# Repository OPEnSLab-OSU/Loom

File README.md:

<b>THIS VERSION OF LOOM HAS BEEN DEPRECATED AND IS NO LONGER BEING SUPPORTED, ANY BUGS YOU MAY ENCOUNTER WILL NOT BE FIXED PLEASE USE Loom 4</b>
https://github.com/OPEnSLab-OSU/Loom-V4

<p align="center">
    
  </a>
</p>

<h3 align="center">Loom</h3>
<p align="center">
  An Internet of Things Rapid Prototyping System for applications in environmental sensing
  <br>
  <a href="http://www.open-sensing.org/project-loom">Project Page</a>
  ·
  <a href="https://openslab-osu.github.io/Loom/html/index.html">Documentation</a>
  ·
  <a href="https://github.com/OPEnSLab-OSU/Loom/wiki">Lab Wiki</a>
  ·
  <a href=https://github.com/OPEnSLab-OSU/Loom/wiki/Quick-Start>Quick Start</a>
   ·
  <a href=https://github.com/OPEnSLab-OSU/Loom/wiki/Configuration>Configuration</a>
</p>

## Table of Contents

- [Table of Contents](#table-of-contents)
- [Introduction](#introduction)
- [Objectives](#objectives)
- [Key Features](#key-features)
- [Installing Arduino and Loom](#installing-arduino-and-loom)
- [Quick Start](#quick-start)
- [Common Pin Allocations](#common-pin-allocations)
- [Hardware Support](#hardware-support)
- [Documentation](#documentation)
- [Contributing](#contributing)
- [Versioning](#versioning)
- [Resources](#resources)
    - [Custom/Modified Libraries used by Loom](#custommodified-libraries-used-by-loom)
- [License](#license)

## Introduction

Loom is an ongoing multidisciplinary collaboration of the OPEnS Lab with a team of 20+ Computer Science and Electrical Engineering students to create a fully open source, modular, user friendly, sensor/actuator Arduino library and ecosystem. The project enables environmental research and conservation communities to overcome significant technical hurdles for creating new environmental, agricultural, and ecological instrumentation to measure, monitor, automate, and understand our world. 

## Objectives

- Design a "plug and play" sensor/actuator system
- Simple enough for K-12 students and non-technical users to use
- Extensible and programmable enough for engineers to customize
- Create a wide variety of applications by simply connecting modular components
- Make the system wireless, low-power, low latency
- Configure all sensors and actuators on a wireless network using an intuitive graphical user interface
- Interact with data and control signals on a network in realtime
- Make data transmitted from local and remote locations available instantly from anywhere around the world

## Key Features

- Quick to setup an entirely new project
- Code contained in an Arduino library
- System behavior defined with a configuration specification and minimal code
- Extensive customizability for complex applications
- Designed for extensibility
- Variety of sensors and actuators supported 
- Remote data logging to SD and internet in near real time

## Installing Arduino and Loom

[Installing Arduino and Loom Quick Setup](https://github.com/OPEnSLab-OSU/Loom/wiki/Arduino-and-Loom-Quick-Setup)

[Installing Arduino and Loom Manual Setup](https://github.com/OPEnSLab-OSU/Loom/wiki/Arduino-and-Loom-Manual-Setup)

## Quick Start

 [Quick Start Guide](https://github.com/OPEnSLab-OSU/Loom/wiki/Quick-Start)

## Common Pin Allocations

[Common Pin Allocations](https://github.com/OPEnSLab-OSU/Loom/wiki/Common-Pin-Allocations)

## Hardware Support

[Hardware Support](https://github.com/OPEnSLab-OSU/Loom/wiki/Hardware-Support)

## Documentation

[Wiki](https://wiki.open-sensing.org/doku.php?id=loom) for general documentation not on GitHub or in Doxygen document

[Doxygen generated documentation Version 1](https://openslab-osu.github.io/Loom/html/index.html) for more verbose documentation that is designed for developers

[Doxygen generated documentation Version 2](https://openslab-osu.github.io/Loom/index.html) for more user-friendly documenation that is designed for end-users

***Note***: The documentation does not currently update automatically, if would want to be sure you have the most up to date version of the documentation, you can run Doxygen to manually generate a local copy of the documentation. See the Doxygen website on how to [Install Doxygen](http://www.doxygen.nl/manual/install.html) and [Doxygen Usage](http://www.doxygen.nl/manual/doxygen_usage.html). 

Once installed, the run `doxygen Doxyfile` from the command line (from Loom directory) to generate the documentation. To view, open the `Loom/html/index.html` file in a browser.

## Contributing

Is there hardware support or other feature you would like to add to Loom? Follow our [Guide to contributing to Loom](https://github.com/OPEnSLab-OSU/Loom/wiki/Contributing-to-Loom)

## Versioning

Loom aims to follow [Semantic Versioning](https://semver.org) 

## Resources

- [Project Page](http://www.open-sensing.org/project-loom) for Loom on OPEnS lab website
- [GitHub Organization](https://github.com/OPEnSLab-OSU) for all OPEnS Lab projects
- [Loomify](https://github.com/OPEnSLab-OSU/Loomify) An npm package to drive the backend Loom Tag Format parsing and Loom Library github interactions.
- [Loom Configurator](https://github.com/OPEnSLab-OSU/Loom_Configurator) A WebApp designed for designing and exporting loom configurations
- [Loom-Network](https://github.com/OPEnSLab-OSU/Loom-Network) Arduino networking library designed for use with any wireless radio
- [Loom-Auxilliary](https://github.com/OPEnSLab-OSU/Loom_Auxiliary) General Loom and lab non-code files
- [Max-Loom2](https://github.com/OPEnSLab-OSU/Max-Loom2) MaxMSP interfaces for Loom interactivity

#### Custom/Modified Libraries used by Loom

- [OPEnS_RTC](https://github.com/OPEnSLab-OSU/OPEnS_RTC) A modified arduino library for with support for a variety of RTCs
- [SSLClient](https://github.com/OPEnSLab-OSU/SSLClient) Arduino library to add SSL functionality to any Client class 
- [EthernetLarge](https://github.com/OPEnSLab-OSU/EthernetLarge) Ethernet Library for Arduino, modified to support larger buffers for SSLClient

## License 

Loom is licensed under [GNU General Public License v3.0](https://github.com/OPEnSLab-OSU/Loom/blob/master/LICENSE)

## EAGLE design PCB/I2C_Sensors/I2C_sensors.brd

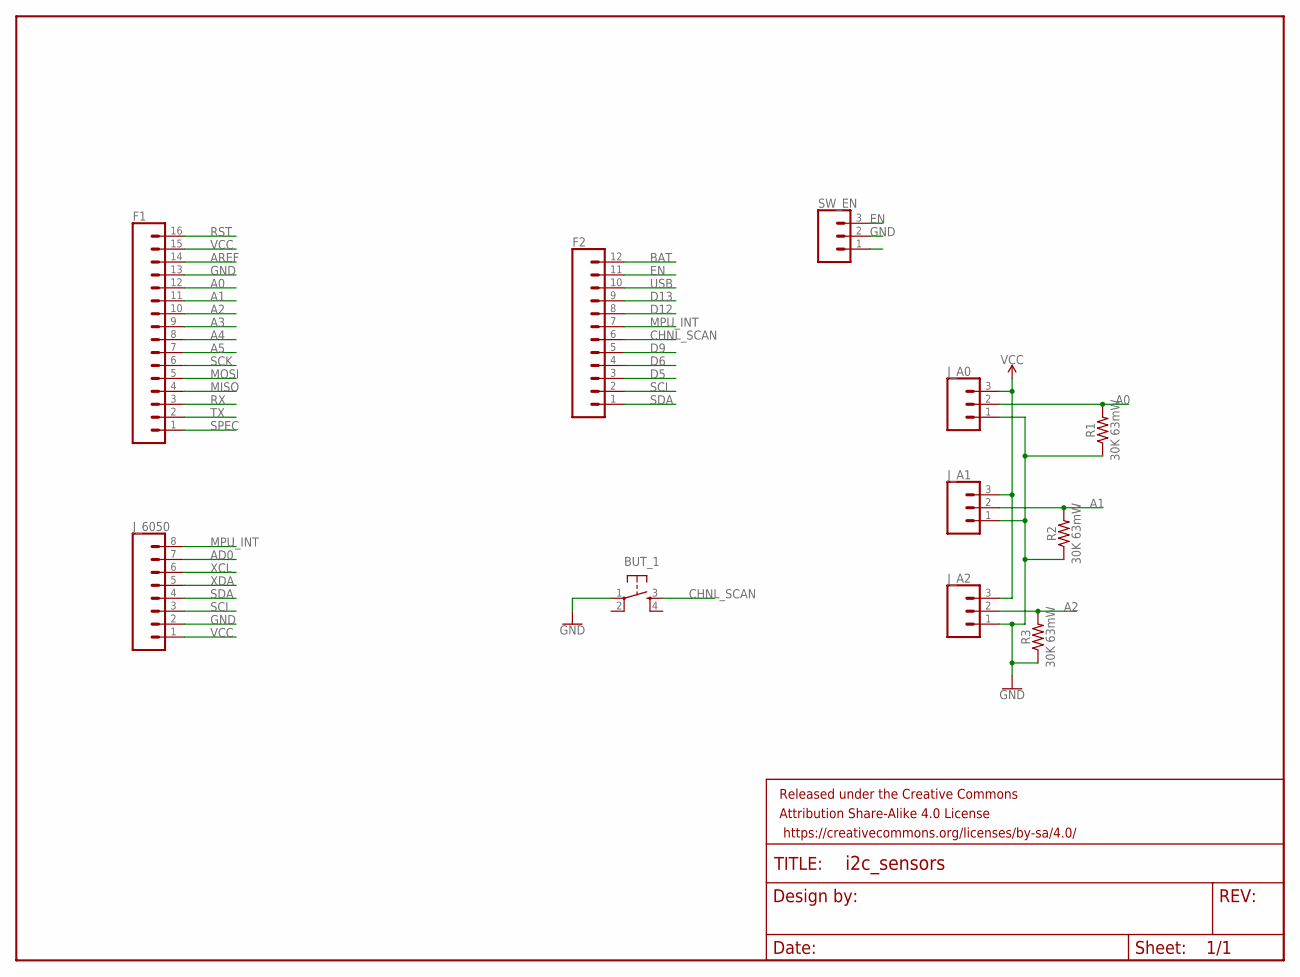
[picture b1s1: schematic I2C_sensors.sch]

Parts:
BUT_1: TAC_SWITCHPTH; TACTILE-PTH
F1: CONN_16; 1X16
F2: CONN_12; 1X12
FRAME1: FRAME-LETTER; CREATIVE_COMMONS
J_6050: CONN_08"; 1X08
J_A0, J_A1, J_A2: CONN_03JST-PTH-VERT; JST-3-PTH-VERT
R1, R2, R3: 30K 63mW; 0805
SW_EN: CONN_03; 1X03

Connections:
A0: F1.12, J_A0.2, R1.2
A1: F1.11, J_A1.2, R2.2
A2: F1.10, J_A2.2, R3.2
A3: F1.9
A4: F1.8
A5: F1.7
AD0: J_6050.7
AREF: F1.14
BAT: F2.12
CHNL_SCAN: BUT_1.3, F2.6
D5: F2.3
D6: F2.4
D9: F2.5
D12: F2.8
D13: F2.9
EN: F2.11, SW_EN.3
GND: BUT_1.1, F1.13, J_6050.2, J_A0.1, J_A1.1, J_A2.1, R1.1, R2.1, R3.1, SW_EN.2
MISO: F1.4
MOSI: F1.5
MPU_INT: F2.7, J_6050.8
RST: F1.16
RX: F1.3
SCI: F2.2, J_6050.3
SCK: F1.6
SDA: F2.1, J_6050.4
SPEC: F1.1
TX: F1.2
USB: F2.10
VCC: F1.15, J_6050.1, J_A0.3, J_A1.3, J_A2.3
XCL: J_6050.6
XDA: J_6050.5

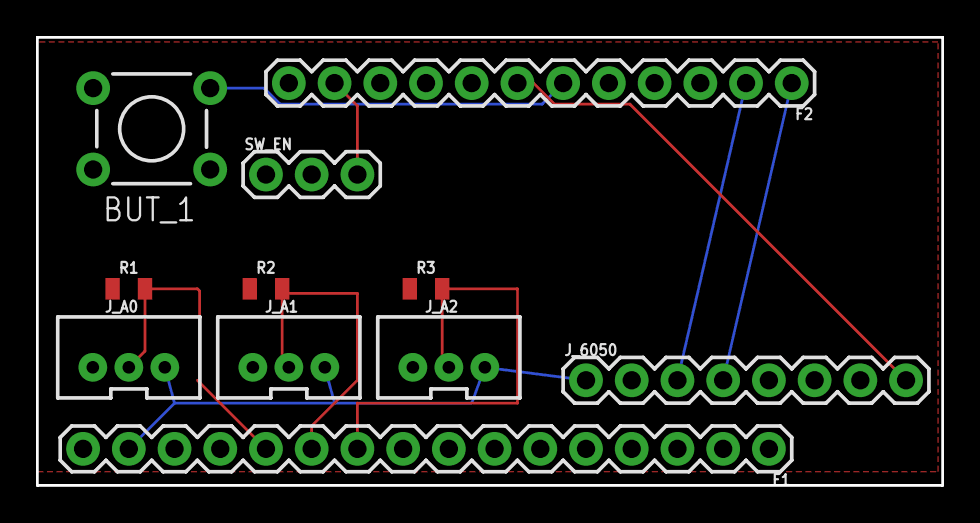
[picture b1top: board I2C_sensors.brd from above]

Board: 2 copper layers, 50.3 x 24.9 mm, 12 parts (0 on the bottom side), 10 nets.

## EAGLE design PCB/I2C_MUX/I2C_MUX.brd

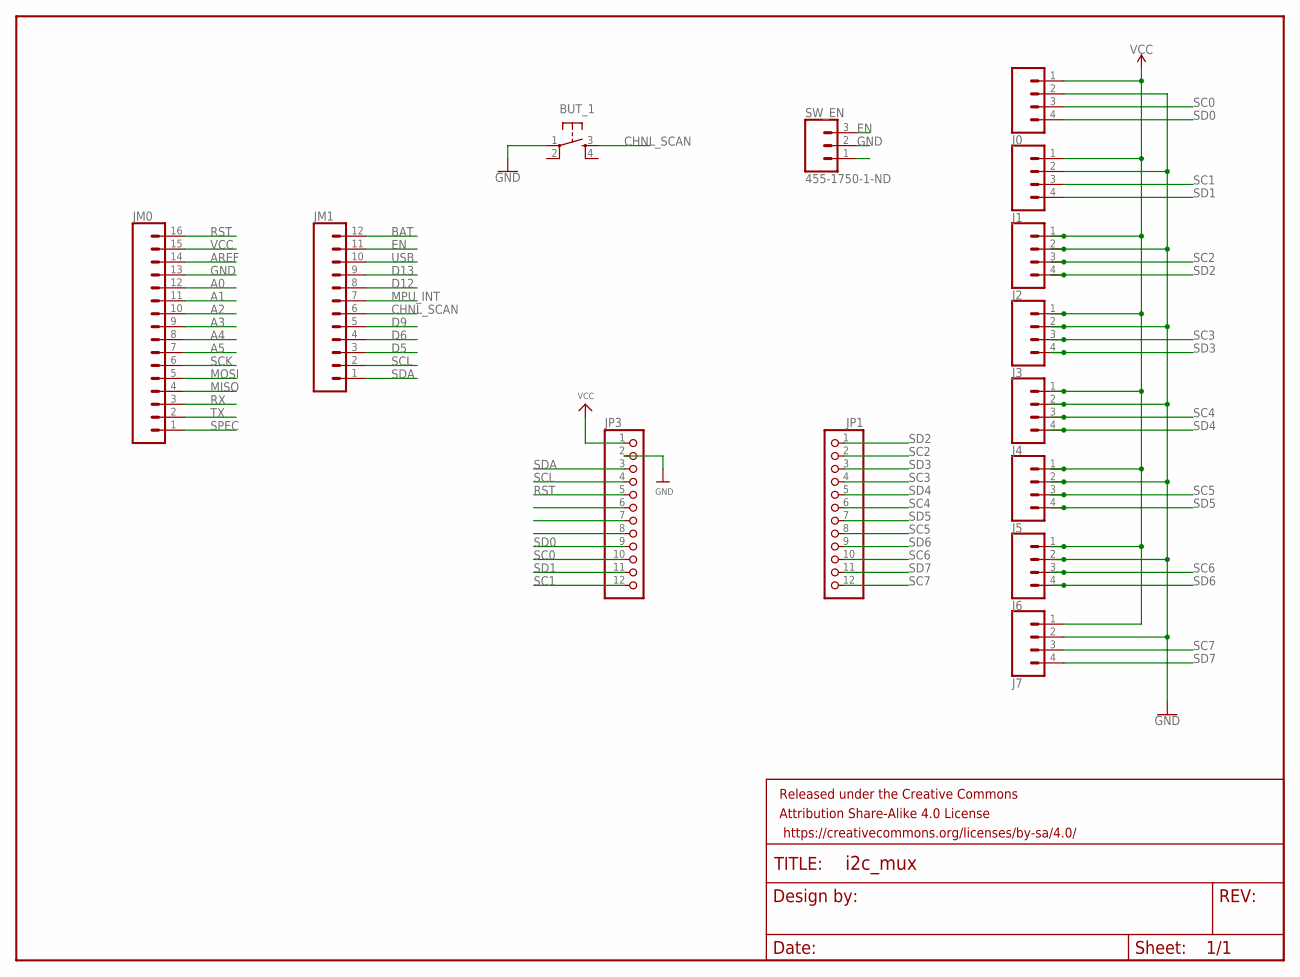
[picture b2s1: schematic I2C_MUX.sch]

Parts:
BUT_1: TAC_SWITCHPTH; TACTILE-PTH
FRAME1: FRAME-LETTER; CREATIVE_COMMONS
J0, J1, J2, J3, J4, J5, J6, J7: CONN_04POLAR; MOLEX-1X4
JM0: CONN_16; 1X16
JM1: CONN_12; 1X12
JP1, JP3: HEADER-1X12; 1X12_ROUND
SW_EN: 455-1750-1-ND; 1X03

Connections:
A0: JM0.12
A1: JM0.11
A2: JM0.10
A3: JM0.9
A4: JM0.8
A5: JM0.7
AREF: JM0.14
BAT: JM1.12
CHNL_SCAN: BUT_1.3, JM1.6
D5: JM1.3
D6: JM1.4
D9: JM1.5
D12: JM1.8
D13: JM1.9
EN: JM1.11, SW_EN.3
GND: BUT_1.1, J0.2, J1.2, J2.2, J3.2, J4.2, J5.2, J6.2, J7.2, JM0.13, JP3.2, SW_EN.2
MISO: JM0.4
MOSI: JM0.5
MPU_INT: JM1.7
RST: JM0.16, JP3.5
RX: JM0.3
SC0: J0.3, JP3.10
SC1: J1.3, JP3.12
SC2: J2.3, JP1.2
SC3: J3.3, JP1.4
SC4: J4.3, JP1.6
SC5: J5.3, JP1.8
SC6: J6.3, JP1.10
SC7: J7.3, JP1.12
SCK: JM0.6
SCL: JM1.2, JP3.4
SD0: J0.4, JP3.9
SD1: J1.4, JP3.11
SD2: J2.4, JP1.1
SD3: J3.4, JP1.3
SD4: J4.4, JP1.5
SD5: J5.4, JP1.7
SD6: J6.4, JP1.9
SD7: J7.4, JP1.11
SDA: JM1.1, JP3.3
SPEC: JM0.1
TX: JM0.2
USB: JM1.10
VCC: J0.1, J1.1, J2.1, J3.1, J4.1, J5.1, J6.1, J7.1, JM0.15, JP3.1

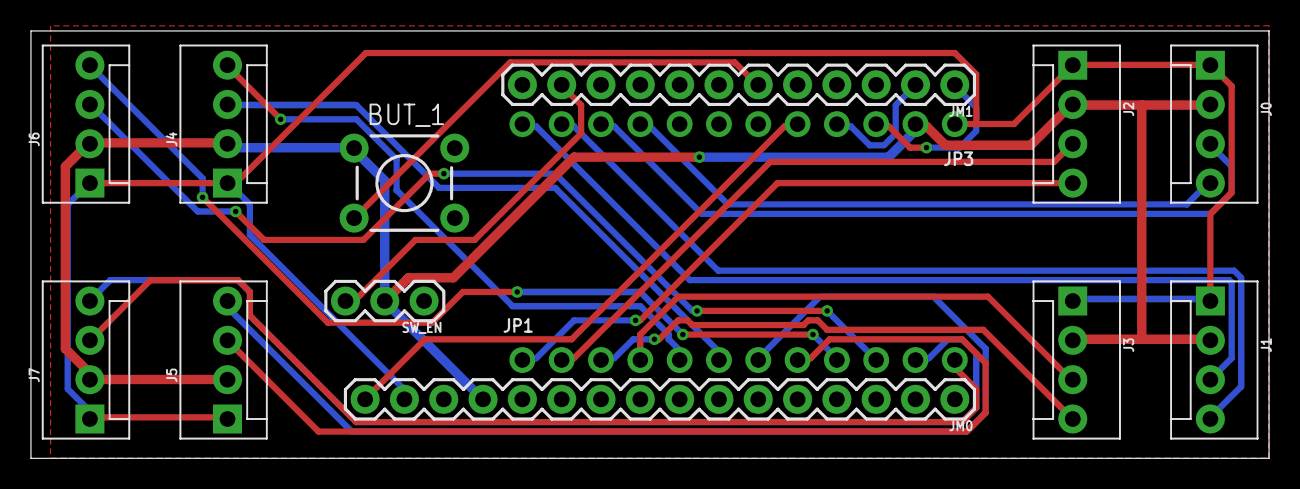
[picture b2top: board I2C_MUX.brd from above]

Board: 2 copper layers, 80.0 x 27.6 mm, 15 parts (0 on the bottom side), 23 nets.

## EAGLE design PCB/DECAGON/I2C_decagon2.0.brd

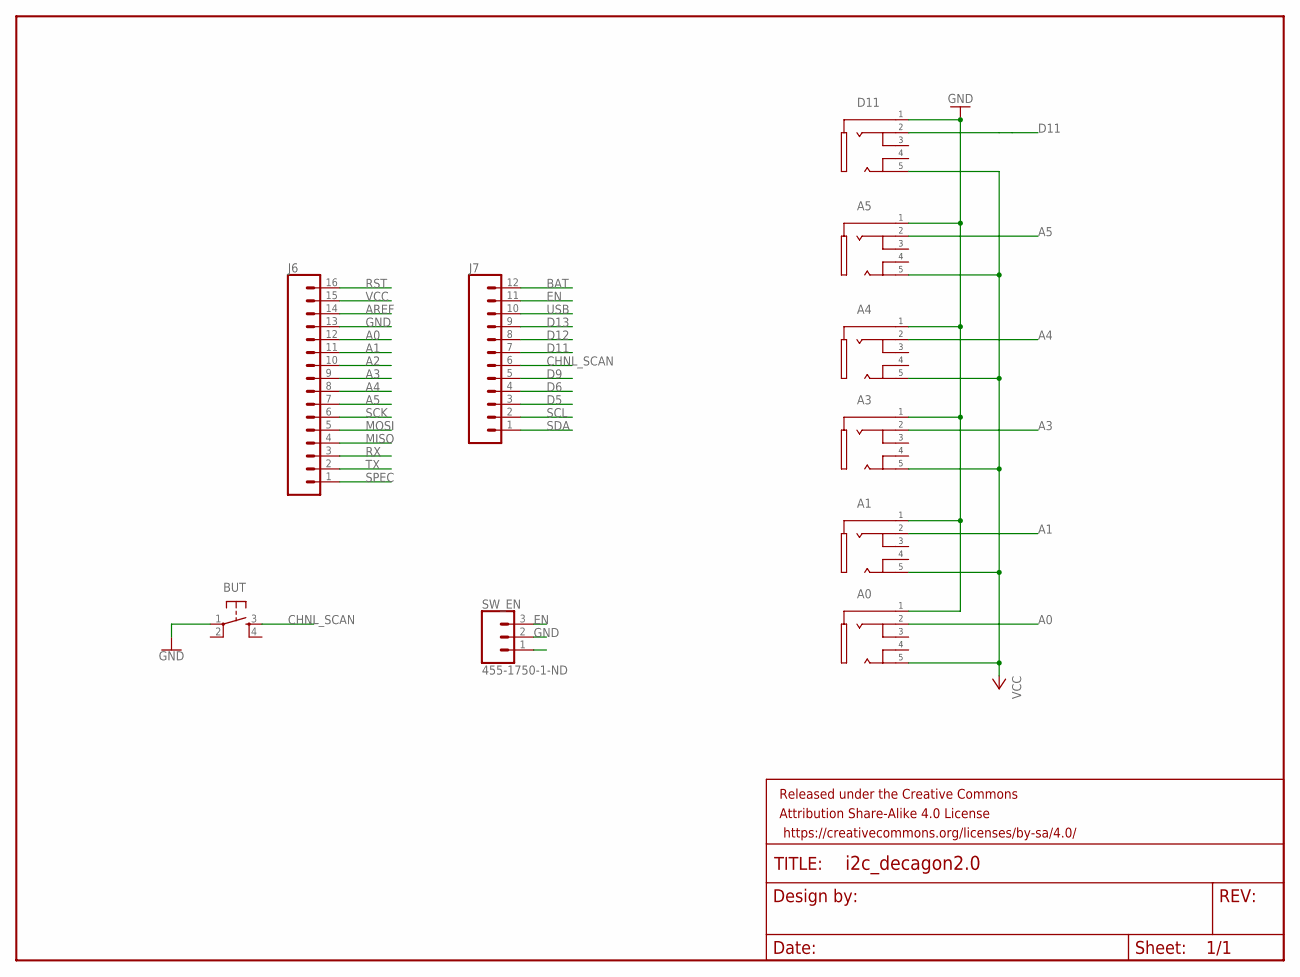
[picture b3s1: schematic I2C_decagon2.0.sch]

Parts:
A0, A1, A3, A4, A5: JW-PJ-307-5H
BUT: TAC_SWITCHPTH; TACTILE-PTH
D11: JW-PJ-307-5H
FRAME1: FRAME-LETTER; CREATIVE_COMMONS
J6: CONN_16; 1X16
J7: CONN_12; 1X12
SW_EN: 455-1750-1-ND; 1X03

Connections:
A0: A0.2, J6.12
A1: A1.2, J6.11
A2: J6.10
A3: A3.2, J6.9
A4: A4.2, J6.8
A5: A5.2, J6.7
AREF: J6.14
BAT: J7.12
CHNL_SCAN: BUT.3, J7.6
D5: J7.3
D6: J7.4
D9: J7.5
D11: D11.2, J7.7
D12: J7.8
D13: J7.9
EN: J7.11, SW_EN.3
GND: A0.1, A1.1, A3.1, A4.1, A5.1, BUT.1, D11.1, J6.13, SW_EN.2
MISO: J6.4
MOSI: J6.5
RST: J6.16
RX: J6.3
SCK: J6.6
SCL: J7.2
SDA: J7.1
SPEC: J6.1
TX: J6.2
USB: J7.10
VCC: A0.5, A1.5, A3.5, A4.5, A5.5, D11.5, J6.15

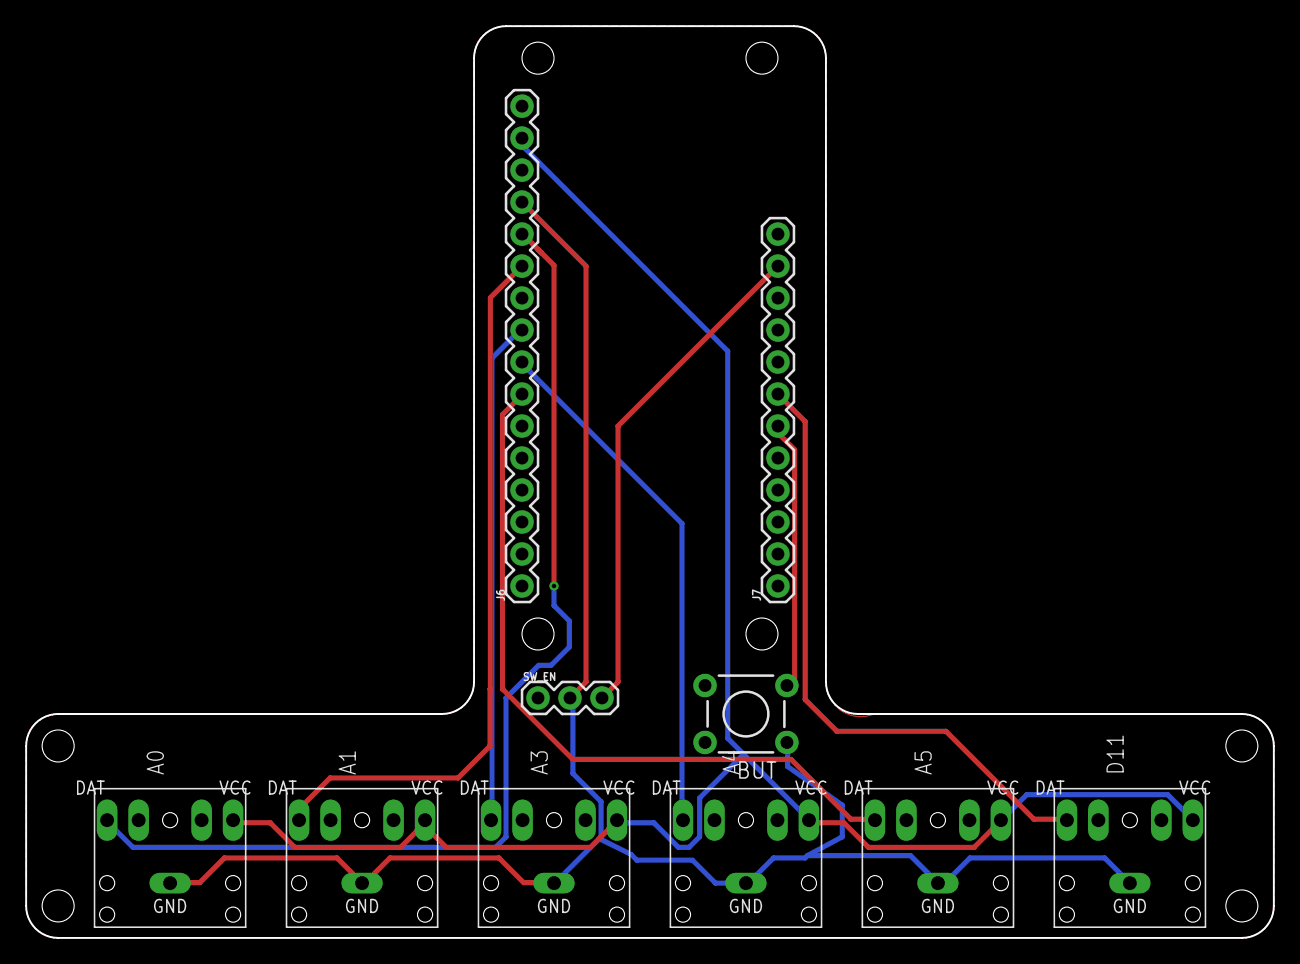
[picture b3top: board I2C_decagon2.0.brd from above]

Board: 2 copper layers, 99.1 x 72.4 mm, 11 parts (0 on the bottom side), 10 nets.

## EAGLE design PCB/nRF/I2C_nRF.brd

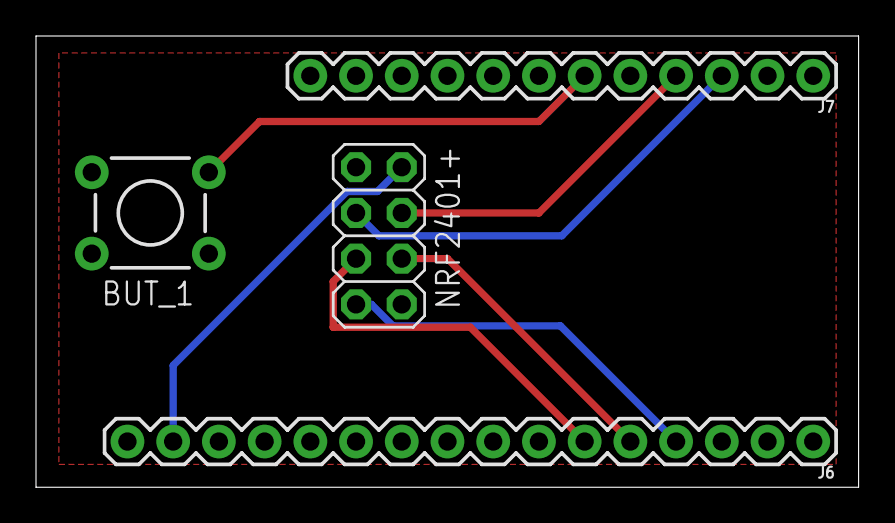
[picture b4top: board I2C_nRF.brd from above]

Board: 2 copper layers, 45.7 x 25.1 mm, 5 parts (0 on the bottom side), 8 nets.

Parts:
BUT_1: TACTILE-PTH
FRAME1: FRAME-LETTER; CREATIVE_COMMONS
J6: 1X16
J7: 1X12
NRF2401+: 2X04

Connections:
CHNL_SCAN: BUT_1.3, J7.6
D5: J7.3, NRF2401+.3
D6: J7.4, NRF2401+.4
GND: BUT_1.1, J6.13, NRF2401+.1
MISO: J6.4, NRF2401+.7
MOSI: J6.5, NRF2401+.6
SCK: J6.6, NRF2401+.5
VCC: J6.15, NRF2401+.2

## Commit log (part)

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2020-01-14 tightening includes and moving dependencies into appropriate locations
2020-01-14 Moving excessive special comments into source files, recomend using jump to def
2020-01-16 reworked CommPlat interface to be more friendly with radio sleep, need to fix compilation errors
2020-01-16 Created WarmUp mixin and manager.
2020-01-16 Switched to non-caching registration
2020-01-17 fix typos preventing compilation
2020-01-17 Revert "reworked CommPlat interface to be more friendly with radio sleep, need to fix compilation errors", as I committed it to the wrong branch
    This reverts commit d4e44bfb0cdaa9efa9434945bd7db0422b1b4160.
2020-01-17 Added niave warmup time reporting.
2020-01-19 Corrected constructors for all modules to back reference to LoomManager
2020-01-19 Compiles with LoomManager backreference
2020-01-22 Broken Serial Sensor
2020-01-22 Corrected hastily find/replaced urls.
2020-01-22 Corrected implementation of Warmup_Manager to have protected static cast registration as well as implemented power and power managager.
2020-01-25 Removed outdated code to add data to json
2020-01-27 Cleaned up new code
2020-01-27 Package only needs to store returned values, additionally, reduces the types being inserted into the JSON Doc
2020-01-28 Compileable version of K30/SerialSensor
2020-01-29 Modified multiplexer to use power mixin rather than inheritance.
2020-01-30 remove redundant ADS1115 example
2020-02-08 Added function to get LoRa Rssi
2020-02-10 Revert "Revert "Merge branch 'master' into SitkaNetV2""
    This reverts commit 32ee07299223c5bcfe8d062e9ec56037f620a80e.
2020-02-11 minor updates to example sketch
2020-02-13 fix a typo with the SD Sleep example
2020-02-18 Add functions in LoRa to allow sending/recieving raw payloads, as escape hatch for SitkaNet to address https://github.com/OPEnSLab-OSU/Loom/issues/69
2020-02-19 Fixed key overwriting on Analog module's json package as well as cleaned up serial printing.
2020-02-20 Add error message regarding this issue: https://github.com/OPEnSLab-OSU/Loom/issues/74 A fix is still needed.
2020-02-20 Increase JSON buffer size to allow large JSON packets
2020-02-21 Ensure multiplexer is reactivated on power_up test success
2020-02-28 Remove all powerup/down actions in sleep manager not directly related to sleep (see https://github.com/OPEnSLab-OSU/Loom/issues/76)
2020-03-03 Add memory warnings to address https://github.com/OPEnSLab-OSU/Loom/issues/81
2020-03-10 Added return status to LogPlat::log
2020-03-11 Remove spool from codebase
2020-03-12 Finish first pass of ADS1115 implementation
2020-03-12 Fixed a signed number overflow, finished implementation
2020-03-12 Remove dead internetplat code
2020-03-27 Add URL for the FW6ROU7IYEQ85OL.ino reference
2020-04-08 Cleaning up some mess
2020-04-08 Edit more stuff and cleaning the mess
2020-04-09 Fixed backreferencing LoomManager from child module to Loom Module base class.
2020-04-12 Fix the declaration error for K30, still working on it
2020-04-12 It complies, but doesn't work
2020-04-12 forgot to add ;
2020-04-15 Support for SparkFun LTE Shield
2020-04-15 Fix some errors and add a TODO on K30.cpp file
2020-04-24 Comment changes and config fix
2020-05-20 Comments
    Cleaning up comments for copyright, functionality details, and exampe description.
2020-06-17 modify the K30 Example
2020-06-17 Modify the Example code for K30 Sensor
2020-06-24 Update to LTE
    Provided functionality for the Hypnos board, power up and power down
2020-06-25 Update to Travis
2020-06-26 Receive_Blocking_Raw and Transmit_Raw example code done for Issue 69. Need to test
2020-07-01 Grammar, need to test
2020-07-01 Reverting setup.h
2020-07-07 Updates to install scripts for seperate support
2020-07-07 Fix K30 documentation error
2020-07-07 Documentation updated, but missing two sensors documentation
2020-07-07 Removing sleepydog, Chet's wifi path, and added examples
2020-07-10 Updates to bug in install scripts
2020-07-11 Updates to install script and Doxygen
2020-07-20 Initial Loomified RFID Tag Reader
2020-07-20 Added Spool to Loom
2020-07-23 Adjustments for the RFID project
2020-07-24 Batch Logging and Transmit Code
2020-07-25 Update Spool Code
2020-07-27 Updates with print module and get batch json
2020-07-27 Trying adding Spool to Loom
2020-07-27 Working templated factory
2020-07-28 Adding required field to work with new factory
2020-07-28 little changes
2020-07-28 Not sure for some parts of the Spool
2020-07-29 More structural changes and updates to comments
2020-07-30 Update config.h
    Typo fix
2020-07-30 Fixes to batch
2020-07-30 minor changes
2020-07-30 Adding documentation to new template factory
2020-07-31 Updates to Batch Example
2020-08-06 Spool with Loom is Complete!
2020-08-06 Add Example for Spool
2020-08-06 Updates to Examples
2020-08-06 RFID Changes
2020-08-07 Updates to RFID naming
2020-08-07 Added comments for SpoolPublish member variables
2020-08-10 Remove TODO comment
2020-08-12 Modify some parts
2020-08-13 Updates to RFID constructor
2020-08-14 Update Spool Example links
2020-08-17 Fixed comments / added power rail global variables
2020-08-26 split_send is complete
2020-08-26 Almost done
2020-08-26 Fix the error with size calculation
2020-08-27 Added comments
2020-08-27 Need to make it better
2020-09-01 Correct measurements and trying to solve bit prob
2020-09-02 Final updates
2020-09-08 Solve issue #123 with false time read
2020-09-13 Fix some odd member of pointer syntax
2020-09-13 Fix header include formatting
2020-09-13 Add 'registered' static variable to modules
2020-09-13 Static registration based on flags
2020-09-13 Fix module creation lookup table names
2020-09-14 Make is_registered members const
2020-09-14 Radio toggle set up
2020-09-14 Sensor toggle setup
2020-09-14 Max toggle set up
2020-09-14 Toggle internet set up
2020-09-14 Allow Loom Debug prints to be disabled
2020-09-14 Some cleanup
2020-09-14 Print statements to show the issue with json size
2020-09-15 These should also be disabled with Max
2020-09-15 Remove conditional registry flags I missed
2020-09-15 Default time is now UTC rather than Local
2020-09-16 Fix to allow analog pins work for interrupts
2020-09-17 Switch registration to macro
2020-09-17 Factory properly handles module configs with: param list, default or implicit default
2020-09-17 Cleaner methods of module access from manager
2020-09-17 Forgot to remove library toggle flags
2020-09-17 Default time is now UTC with able to measure local
2020-09-18 Remove Loom_ prefixes. Other than RTC which would collide with existing names. Modified OPEnS_RTC PCF8523 class to RTC_PCF8523
2020-09-18 Rewrite print macros with C++17 fold expressions
2020-09-18 Minor cleanup in Analog.cpp
2020-09-19 Temporarily change some class names
2020-09-19 Rename LoomModule -> Module now that Loom has namespace
2020-09-19 Formatting improvements
2020-09-19 Remove Module::Type and Module::Category enums
2020-09-20 Update the false failed statement
2020-09-22 Updated Other stuff rather than commplat
2020-09-28 Fix some invalid configs
2020-09-28 Create equivalent yaml configs
2020-09-29 Update examples
2020-10-09 Interrupt fix and example
2020-10-15 Rename Local Time to LocalTime
2020-10-15 Modify and Add Example code for RTC
2020-10-19 Add an validation for custom time setup
2020-10-29 A better temporary solution for #23
2020-11-02 Updates on notification
2020-11-11 Fix check for device manager
2020-11-11 Fix examples, Manager::get returns pointers
2020-11-17 FeatherFault integration, diagnostics framework
2021-02-05 Inital V3 Compiling
2021-02-15 Added getter function for humidity
2021-02-20 Remove old implementations of add_config
2021-02-20 Fix examples
2021-02-21 Add functionality to read/save config to flash
2021-02-21 Ignore config_str.h files generated with parsing json/yaml configs
2021-02-21 Add example of saving config to flash memory
2021-02-21 Switch examples to use 'Feather' as name of Loom Manager instance
2021-02-21 Some MaxSub/MaxPub fixes
2021-02-22 Clean up Relay.cpp
2021-02-23 Updated config
2021-03-16 Minor corrections to cherrypick
2021-03-16 Move LOOM_FLASH_CONFIG define to Manager.h
2021-03-16 Make APWifi module name consistent with the branch's naming scheme
2021-03-18 Add AP Wifi to factory
2021-03-18 Add access point example
2021-03-18 Switch MaxSub/Pub to use any InternetPlat (ignores 700X val in config currently)
2021-03-18 Add access point to client mode with saved config example
2021-03-21 Save the rest of Manager settings in flash
2021-04-05 Removing excess mark statements and updating examples to match V3
2021-04-09 Update Loom.h
    Adding getter function for better readability and writeability
2021-04-09 Changed example sketches
    updated example sketches to use new function names.
2021-05-09 Actually still want these ifs
2021-06-12 Doxygen should generate svg graphs
2021-06-13 Add script to parse modules to build schema of valid Loom configuration settings
2021-08-17 Added branch
    Changed the Loom.h to prevent shallow copies of feather/modules.
2021-09-01 Fixed halting issue for PCF8523.cpp RTC
2021-09-01 Fixed GoogleSheets Publish
    added fix for googlesheets publish causing SSL errors.
    added fix for loom.h including shallow modules
2021-09-03 Fixed typos and fixed Sleep example problem not enableing hypnos pins
2021-09-08 LoRa Update
    Added getter function for RSSI, LoRa settings optimized for longer range, shorter transmission rate
2021-09-09 Another fix in examples
2021-09-09 Alas, more example fixes
2021-09-09 Adjusted paramter in nRF example to accommodate previous commit's nRF code change.
2021-09-09 Removed include statements from Loom and Multiplexer after previous commit that deleted TLS2561 support
2021-09-14 Added fix for SSL client.
    I don't know how this wasn't already here. This fixes the repeating error problem.
2021-09-20 Fixing incomplete Manager.pause() refactor
2021-09-20 Fixed bug with Manager.add_data() failing to manually add multiple data entries with the same module name
2021-09-20 Added less ambiguous print for when module keys are invalid in config.h. Removed residual print in Package.cpp
2021-10-04 Changed default SD GPIO pin from 10 to 11
2021-10-12 Changed SD chip select pin from 10 to 11 in BatchSD and some SD examples
2021-10-14 Started to implement SDI12, using SitkaNet's dirty implementation
2021-10-18 Added print_measurements command
2021-10-19 SDI12 sensor defaults
2021-10-19 Tried another fix with ADS1114.cpp problems
2021-10-25 Finalizing Decagon implementation
2021-10-25 Overhauled SDI12/Decagon. Now the SDI12_Sensor modules handle most basic low level communication. Which allows the specific sensor classes to be fairly clean
2021-10-25 Revising Luke's APWiFi module to be Loom 3 compatible
2021-10-27 SD can now log up to 999 files of the same name
2021-10-27 Pushing wills changes which I have merged, idk
2021-10-29 Fixed bad merge of SDI12 sensors
2021-11-10 added teros sensor functionality
2021-11-15 Added functionality for Decagon 5TM
2021-11-18 The amount of errors here are insane
2021-11-20 Added check for sensor type
2021-11-22 Reworked entire SDI protocol into a single object setup. Config imports the SDI_Manager and it then handles and properly inits. The correct modules by pulling the info command on the sensor.
2021-11-22 Removed useless return call
2022-01-19 Initial commit. Everything compiles but still needs to be tested.
2022-01-20 Changed the send address from 1 to 0 in the Transmit FW example. I switched this value around for the Transmit and Receive sketches, so now the Transmit sketch has ID 1, and Receive has ID 0. These n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
2022-01-25 Fixed APWifi constructor, added additional debug information to Max_Pub and Sub
2022-01-28 Updated print statements for send/receive implementations in FW.cpp. This way it should be more clear what a failed send/receive actually means.
2022-01-31 Added MQTT_Pub functionality
2022-02-11 Changed LoRa module to match the FW module: instance ID is used as the RadioHead ID; print statements have been changed to more accurately reflect possible issues with communication.
2022-02-16 APWifi fix
2022-03-29 Add expected input format to RTC custom time prompts
2022-04-01 Add Loom method to read serial number from Feather M0
2022-04-11 Change conditional for printing header rows to SD
2022-04-14 Modify timestamp logging to include leading zero
2022-05-04 Add simple examples for interrupts
2022-06-08 Integrate MAX31865 into Loom 3
2022-06-09 Minor fix
2022-06-10 Add offset and scale as config options

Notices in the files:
parts and their libraries:
SparkFun-Retired: Licensing: Creative Commons ShareAlike 4.0 International - https://creativecommons.org/licenses/by-sa/4.0
SparkFun-Aesthetics: Released under the Creative Commons Attribution Share-Alike 4.0 License
SparkFun-Aesthetics: https://creativecommons.org/licenses/by-sa/4.0
